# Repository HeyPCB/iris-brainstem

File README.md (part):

# Iris Brainstem

The power and servo hub in the base of Iris: 9 V USB-C PD in, a 6 V / 5 A servo rail laid in stitched copper zones, a 5 V rail, the half-duplex servo bus with ten ports, a speaker amp and a USB-C data port.

Part of [Iris, the human-eyed robot head](https://github.com/HeyPCB/iris), HeyPCB's open robot boards. Designed end to end with the HeyPCB method on
KiCad 10 (headless pipeline, Freerouting 2.4.1); every number below is measured on the files in this repository.
Mentions of `./run.sh`, `docs/rules/`, `blocks/` or `parts/` refer to the heypcb-kicad SDK that produced them.

| Layers | Outline | Parts | Nets | Connections routed | Vias | ERC errors | DRC errors / unconnected / parity |
|---|---|---|---|---|---|---|---|
| 4 | 64 x 80 mm, shaped | 97 | 48 | 230 -> 0 open | 208 | 0 | 0 / 0 / 0 |

**Not fabricated, assembled or powered.**

| | |
|---|---|
| KiCad project | [`kicad/`](kicad/) |
| Gerbers (unzipped and zipped), BOM, CPL, STEP, schematic PDF | [`fab/`](fab/) |
| Mechanism CAD, fit check and system docs | [Iris, the human-eyed robot head](https://github.com/HeyPCB/iris) |
| Renders | [top](media/top.png), [bottom](media/bottom.png) |
| Design process, every step as KiCad rendered it | [`media/design-process.mp4`](media/design-process.mp4) |

Iris Brainstem is board B2 of Iris, a robot head with human-like eyes. It sits flat in the base of
the head and is the head's power, USB and servo hub. It takes 9 V from a USB-C PD charger, makes a
6.0 V / 5 A rail for the ten eye, lid and brow servos and a 5 V rail for the head controller (B1
Cortex), measures the input with an INA226, drives the servos' half-duplex serial bus and the
speaker, and passes a second USB-C port's data up to B1. It was designed with the HeyPCB method on
KiCad 10 (10.0.6), by heypcb-kicad's headless pipeline with Freerouting 2.4.1, from the brief in
`board.json` and section 4.2 of the Iris design spec v0.1 (not published; its binding interconnect and mounting
contracts are in [the Iris system docs](https://github.com/HeyPCB/iris/blob/main/docs/system.md)).

**This board has not been fabricated, assembled or powered, and no firmware for it has been
written.** Everything below is what KiCad, the pipeline and the copper scripts measured on the
design files. Nothing here has been tested on hardware or in the head.

## Role in Iris

Iris has four boards (spec 4): **B1 Cortex** (ESP32-S3, camera, on the eye cradle), **B2
Brainstem** (this board, in the head's base), **B3 Iris ring** (two LED rings) and **B4 Brow**
(forehead sensors). B2 is where power enters the head and where every servo plugs in:

- USB-C **J1 PWR** brings 9 V. Everything in the head is powered from here.
- USB-C **J2 DATA** carries a PC's USB to B1's native USB, and its VBUS powers the logic on its own
  (servos stay off).
- **H1** (JST SH-10) and **H2** (JST SH-7) are the two harnesses to B1: 5V_SYS, USB, the servo bus
  and SERVO_EN on H1; I2C, the INA226's alert and I2S audio on H2 (spec 5).
- **J10-J19** are the servo ports, **J7** the speaker.

## Features

- **USB-C PD sink, 9 V, no firmware.** WCH CH224K (U1) with CFG1, CFG2 and CFG3 tied straight to
  GND, which requests 9 V. There is no configuration resistor to go missing: on the CH224K a
  missing resistor on CFG1 would request 20 V. VDD through 1 kOhm with 1 uF, VBUS sense through
  10 kOhm (WCH's reference schematic). A red **PD OK** LED (D6) hangs on the CH224K's PG output
  (open drain, active low).
- **Input protection and measurement.** SMAJ15A TVS (D1), 5 A Littelfuse NANO2 fuse (F1,
  0451005.MRL), 10 mOhm 1206 shunt (R1) read by an **INA226 at 0x40** (U2, ALERT on H2 pin 4), and
  470 uF on VIN (C3).
- **6V0_SERVO, 5 A.** TPS565208 buck (U3) to 5.93 V (68 k / 10 k on a 0.760 V reference), 3.3 uH
  FXL0630, 3 x 22 uF at the regulator and 470 uF at each servo bank (C1, C2). **Off by default**:
  EN is SERVO_EN from B1 through 1 kOhm with a 100 kOhm pull-down.
- **5V2 and 5V_SYS.** TPS56339 buck (U4) to 5.21 V (54.9 k / 10 k on 0.802 V), 5.6 uH FXL0630, then
  an SS34 (D2) onto 5V_SYS. J2's VBUS joins 5V_SYS through a second SS34 (D3). Neither VBUS is
  ever driven by the board. 5V_SYS goes to B1 on H1 pins 1-2 and to the amplifier.
- **3V3_B2.** AP2112K-3.3 (U6) from 5V_SYS for the INA226, the bus buffers and their pull-ups.
- **Servo bus.** The Waveshare / Feetech auto-direction half-duplex driver: 74LVC1G126 (U7),
  74LVC1G125 (U8) and an MMBT3906 (Q1), 10 k pull-ups on BUS_TX, BUS_RX and BUS_DATA, an ESD5Z5.0 on
  BUS_DATA at each bank (D4, D5). TX is never echoed back to RX.
- **Ten servo ports** (J10-J19), HC-5264-3A vertical (Molex 5264 type), pin 1 BUS_DATA, pin 2
  6V0_SERVO, pin 3 GND, in two banks of five down the left and right edges. **D V G** is printed at
  every port and each port is labelled with its servo ID.
- **Speaker amplifier.** MAX98357A (U9) on B1's I2S, mono (L+R)/2 (1 MOhm on SD_MODE), 9 dB gain,
  from 5V_SYS through a ferrite, to a JST SH-2 (J7). Bridge-tied output: neither wire is ground.
- **USB data port.** J2 with 5.1 kOhm on CC1 and CC2 (a plain sink) and a USBLC6-2SC6 (U5) on D+ /
  D- before H1.
- **Test pads** (1.5 mm, not fitted parts): VIN, 6V0, 5V2, 5V_SYS, 3V3_B2, BUS_DATA, SERVO_EN and
  GND (TP1-TP8).
- **Board:** 64.0 x 80.0 mm, corner fillet 3.0 mm, 1.6 mm, 4 copper layers: F.Cu signal and power
  zones, In1 a solid GND plane, In2 signal with a 6V0_SERVO pour, B.Cu mostly a power layer
  (6V0_SERVO, VIN and 5V_SYS zones, with keep-outs that hold signal tracks off them; 101.5 mm of
  track runs on B.Cu elsewhere). Every part is on the top side. Four non-plated 2.2 mm holes for
  M2 screws.

## Block diagram

```mermaid
flowchart LR
  J1["J1 USB-C PWR"] -->|"VBUS_PD 9 V"| D1["D1 SMAJ15A"]
  J1 -->|"CC, D+/D-"| U1["U1 CH224K<br/>CFG = 9 V"]
  U1 -->|PG| LED["D6 PD OK"]
  J1 -->|VBUS_PD| F1["F1 5 A"] --> R1["R1 10 mOhm"]
  R1 -->|VIN| C3["C3 470 uF"]
  R1 -.->|Kelvin| U2["U2 INA226 0x40"]
  R1 -->|VIN| U3["U3 TPS565208<br/>6V0 5 A"]
  R1 -->|VIN| U4["U4 TPS56339<br/>5V2 3 A"]
  U3 -->|6V0_SERVO| PORTS["J10-J19 servo ports<br/>C1, C2 470 uF"]
  U4 -->|5V2| D2["D2 SS34"] --> SYS(("5V_SYS"))
  J2["J2 USB-C DATA"] -->|VBUS_DATA| D3["D3 SS34"] --> SYS
  J2 -->|"D+/D-"| U5["U5 USBLC6"] --> H1["J5 H1 SH-10 to B1"]
  SYS --> H1
  SYS --> U6["U6 AP2112K 3V3_B2"]
  SYS --> U9["U9 MAX98357A"] --> J7["J7 SPK"]
  H1 -->|"BUS_TX / BUS_RX"| BUS["U7, U8, Q1<br/>half-duplex driver"] -->|BUS_DATA| PORTS
  H1 -->|SERVO_EN| U3
  H2["J6 H2 SH-7 to B1"] -->|I2C| U2
  U2 -->|"ALERT = nINT"| H2
  H2 -->|I2S| U9
```

## Power tree and what the copper carries

```
J1 VBUS_PD, 9 V ─┬─ D1 SMAJ15A to GND
                 └─ F1 5 A ─ R1 10 mOhm (INA226) ─ VIN ─┬─ C3 470 uF
                                                        ├─ U3 TPS565208 ─ 6V0_SERVO ─ C1, C2 470 uF ─ J10-J19 pin 2
                                                        └─ U4 TPS56339 ─ 5V2 ─ D2 SS34 ─┐
J2 VBUS_DATA, 5 V ─ D3 SS34 ────────────────────────────────────────────────────────────┴─ 5V_SYS

5V_SYS ─┬─ H1 pins 1-2 (to B1)
        ├─ FB1 ─ U9 MAX98357A ─ J7 speaker
        └─ U6 AP2112K ─ 3V3_B2
```

The input enters at the rear left (J1), and F1, R1 and C3 stand in one column above it. The servo
buck sits in the middle of the board, with its output node (L1, three 22 uF and C1) on the left,
and the ten ports run down both side edges. The 5V2 buck and the two diodes are at the rear right,
beside J2.

**Load figures** (spec 6, all estimates, none measured): VIN 0.68 A typical, about 4.3 A for
milliseconds (39 W); 6V0_SERVO 0.58 A typical, a 7-servo burst of 4.6 A for milliseconds, 9 A if
every servo stalls (beyond the buck's 5 A by design: firmware must cut torque); 5V_SYS 0.41 A
typical, 1.56 A peak. A 27 W (9 V, 3 A) PD charger is the spec's supply.

**Net classes** (from the brief; a class with a current is never narrowed by the routing ladder):
PDIN 0.6 mm (VBUS_PD, VIN_F, VIN; 0.6 mm is the receptacle's VBUS pads and the bucks' VIN pins),
SERVO 0.8 mm with 0.8 / 0.4 mm vias (6V0_SERVO), SWNODE 0.6 mm (the two switch nodes), RAIL5V
0.6 mm (5V2, 5V_SYS), USBVBUS 0.6 mm (VBUS_DATA). The tracks only connect the path. The current is
carried by the zones below.

### Power zones

After routing reaches 0 open, the pour stage lays the plan pours (GND on F.Cu, B.Cu and In1,
6V0_SERVO on In2) and then the brief's `board.zones`: each a named net's copper over a region on
chosen layers, above the plan pours, with every pad joined solid, and where the zone has a
`stitch` pitch, its own 0.6 / 0.3 mm via lattice. Board coordinates are mm from the outline's
top-left corner (y = 0 is the front edge). Every reason is also in `board.json`.

| Zone | Net | Layers | Region | Priority | Vias placed |
|---|---|---|---|---|---|
| `vbus_pd` | VBUS_PD | F.Cu, B.Cu | J1's VBUS pads, D1's cathode, F1's input pad (x 9.6-21.6, y 64.4-71.7) | 1 | 20 at 1.2 mm |
| `vin_f` | VIN_F | F.Cu | F1's output pad to R1, and the INA226's IN+ resistor (x 14.6-19.7, y 57.6-62.7) | 2 | - |
| `vin_col` | VIN | F.Cu, B.Cu | R1's VIN pad, C3's + pad, the INA226's IN- / VBUS taps (polygon in x 5.4-19.7, y 51.6-63.4) | 3 | 27 at 1.2 mm |
| `vin_band` | VIN | B.Cu | from the input column to both buck inputs (x 9.6-44.8, y 44.9-57.4) | 2 | - |
| `vin_u3`, `vin_u4` | VIN | F.Cu, B.Cu | each buck's VIN pin and input capacitors | 10 | 4 and 5 at 1.2 mm |
| `v6_b` | 6V0_SERVO | B.Cu | a U: the left bank strip, a bar along the front (y 7.3-12.5), the right bank strip | 5 | - |
| `v6_node` | 6V0_SERVO | F.Cu, B.Cu | L1's output pad, the three 22 uF and C1 (x 14.6-23.0, y 31.6-44.7) | 6 | 8 at 1.2 mm |
| `v6_bank_l`, `v6_bank_r`, `v6_c2` | 6V0_SERVO | F.Cu | the V pins of each bank (x 4.6-7.45 and 56.55-59.4, y 12.5-57.0) and C2 | 7, 8 | - |
| `gnd_out6`, `gnd_in6`, `gnd_in5` | GND | F.Cu | the GND sides of the servo buck's output and input capacitors and of the 5V2 buck's input | 9 | 12, 5 and 0 at 1.2 mm |
| `gnd_front`, `gnd_mid`, `gnd_rear` | GND | F.Cu, B.Cu | the front strip, the middle and the rear right, where the plan pour would otherwise have no vias | 0 | 16, 21 and 51 at 2.4 mm |
| `v5_spine` | 5V_SYS | B.Cu | from D2 / D3 at the rear, up the right of the middle (x 45.4-50.8) to H1 | 12 | - |
| `v5_front`, `v5_link_*` | 5V_SYS | F.Cu (+ B.Cu) | H1's pins 1-2, and the three places the spine meets F.Cu (D2, D3, H1) | 12, 13 | 3, 5 and 3 at 1.2 mm |
| `sw_6v0`, `sw_5v2` | SW_6V0, SW_5V2 | F.Cu | the gap between each buck's SW pin and its inductor | 11 | - |
| `v5v2_out` | 5V2 | F.Cu | L2's output pad, the two 22 uF and D2's anode (polygon in x 30.4-36.6, y 51.6-60.4), left of VIN's F.Cu track to U4 | 14 | - |

B.Cu is kept free of signal tracks under these zones by seven `board.keepouts` rectangles
(`bcu_*`), and In2 is kept free of tracks where the VBUS_PD, VIN and the servo buck's via fields
need room (`in2_*`): a stitch via must clear other nets' tracks on every layer. `gnd_in5` found no
via site (U4's GND pins reach In1 through the plan's own vias). Any GND zone stops the plan's GND
stitcher, so the plan's stitching count is 0 and the GND zones stitch themselves. The silkscreen
then displaced 25 GND stitching vias under its text, which leaves **208 vias** on the board (*read
off the board*: 206 of 0.6 / 0.3 mm and 2 of 0.8 / 0.4 mm; 53 of them are routing vias).

### Measured copper on the current path

`copper.py` (KiCad's Python) lists every track, via and pour of each power net on the final board
and exports the copper (tracks, pads, plan pours and zones) as polygons. `copper_cut.py` (any
Python with numpy and scipy) rasterises that copper on a 0.1 mm grid and finds, for each link of
the path, the **narrowest cross-section the link's whole current must pass**: a max-flow / min-cut
from the link's source pads to its sink pads, over every layer, with tracks, zones and via barrels
together, in parallel. Outer copper is taken as 35 um, inner as 17.5 um (JLCPCB's standard 4-layer
build), via plating as 25 um. Each cut is rated with `heypcb_kicad.route.ipc2221_amps` (IPC-2221,
I = k dT^0.44 A^0.725), per layer, summed. Each link is cut a second time with the copper within
1 mm of its pads counted as the pads ("beyond the pads"): that rates the board's own copper between
the parts, apart from the parts' fixed lands. Both scripts are copies of quack_core's, adapted.

| Link | From, to | Narrowest cross-section (35 um equivalent) | 10 C rise | **20 C rise** | Beyond the pads, 10 C / 20 C |
|---|---|---|---|---|---|
| VBUS_PD | J1 VBUS pads (A4, A9, B4, B9) to F1.1 | 1.15 mm of F.Cu, at the receptacle's VBUS pads | 2.6 A | **3.6 A** | 9.0 A / 12.2 A (6.23 mm) |
| VIN_F | F1.2 to R1.1 | 4.24 mm of F.Cu | 6.8 A | **9.2 A** | pads adjacent |
| VIN, both bucks | R1.2 to U3 and U4 VIN pins and their input capacitors | 5.09 mm of F.Cu | 7.8 A | **10.6 A** | 9.3 A / 12.6 A (In2 0.25, barrels 6.06) |
| VIN, servo buck | R1.2 to U3.3, C7.1, C8.1 | 3.08 mm: In2 0.39, 4 via barrels 2.69 | 5.5 A | **7.5 A** | 5.5 A / 7.5 A |
| SW_6V0 | U3.2 to L1.1 | 0.80 mm of F.Cu: U3's SW pin | 2.0 A | **2.8 A** | pads adjacent |
| 6V0_SERVO, all ports | L1.2 to J10-J19 pin 2 | 6.09 mm: F.Cu 0.70, 8 via barrels 5.39 | 10.0 A | **13.5 A** | 10.0 A / 13.5 A |
| 6V0_SERVO, each bank | L1.2 (with C11-C13, C1) to J10-J14 or J15-J19 pin 2 | 6.09 mm, the same section | 10.0 A | **13.5 A** | 10.0 A / 13.5 A |
| 6V0_SERVO, bank to bank | J10-J14 pin 2 to J15-J19 pin 2 | 7.61 mm: In2 2.82, B.Cu 4.78 | 10.0 A | **13.5 A** | 13.4 A / 18.2 A |
| GND, ports to servo buck | J10-J19 pin 3 to U3.1, C11-C13 pin 2 | 8.63 mm of F.Cu | 11.4 A | **15.5 A** | 13.3 A / 18.0 A |
| GND, servo buck to input | U3.1, C7.2, C8.2 to J1 GND pads | 2.97 mm of F.Cu | 5.3 A | **7.1 A** | 13.4 A / 18.2 A (F.Cu 5.74, barrels 2.69) |
| 5V2 | L2.2 to D2.2 (anode) | 1.04 mm of F.Cu | 2.5 A | **3.3 A** | 2.5 A / 3.3 A |
| 5V_SYS | D2.1, D3.1 (cathodes) to J5 pins 1-2 | 0.99 mm of F.Cu | 2.4 A | **3.2 A** | 2.4 A / 3.2 A |

*Read off the board* (`copper_cut.json`, `copper.json`) after the full run with
media. "Pads adjacent" means the two terminals are within 2 mm of each other, so the link is the
pads' own gap.

**What this says against spec 6.** At a 10 C rise on 1 oz outer copper:

- **The servo rail has about twice the copper its burst needs.** 6V0_SERVO from L1 to the ports
  rates 10.0 A (13.5 A at 20 C) against the 4.6 A burst and the buck's 5 A limit. The narrowest
  section is at L1's output node, where the F.Cu node meets the eight vias of `v6_node`; past that
  the current spreads over the B.Cu U, the In2 pour and the F.Cu bank strips. The GND return from
  the ports to the buck's output capacitors rates 11.4 A.
- **The input path carries the 4.3 A peak** at a 10 C rise on every board-copper link: VIN_F
  6.8 A, VIN to both bucks 7.8 A, VIN to the servo buck 5.5 A, the GND return from the buck input
  to J1 5.3 A (13.4 A beyond the pads).
- **Two links end on a part's own pins and rate lower by this rule.** VBUS_PD leaves the
  receptacle through its VBUS pads: 1.15 mm of copper at the pads' edges, 2.6 A at 10 C and 3.6 A
  at 20 C, against the 3 A PD contract and the millisecond 4.3 A peaks. Beyond the pads the zone
  is 6.23 mm (9.0 A). SW_6V0 is the TPS565208's 0.8 mm SW pin, 2.0 A by the chart against a 5 A
  switch current. Both are lands fixed by the footprint and well under 2 mm long; IPC-2221's chart
  is for long conductors, so these figures say little about the real limit, and neither was
  measured. The receptacle's current rating was not checked (see *Check before ordering*).
- **5V2 and 5V_SYS** rate 2.5 A and 2.4 A (3.3 A and 3.2 A at 20 C) against the 1.56 A peak.
  H1's two 5V_SYS pins are JST SH contacts rated 1 A each (catalogue rows), 2 A together, which
  the spec's 1.6 A respects.
- Via barrels are rated with the same formula as a plated wall; that is an approximation.

Nothing here is a measured temperature. Measure F1, R1, J1, U3, L1 and the port headers under the
real servo load before trusting any of it. The routed widths of the rest of the power nets, *read
off the board*: VBUS_DATA 0.6 mm (0.45 mm necks at pads, 2 vias), SW_5V2 0.6 mm plus its zone,
VIN's routed tracks 0.6 mm.

## Connectors and pinouts

Every connector follows spec 5 (binding). "Pin n" is pad n of the KiCad footprint. Both harness
cables are **double-ended, same direction** (pin n to pin n), 28 AWG, 150 mm. The SH headers are
side-entry with their mouths at the front edge; the board's header pin counts (10, 7, 2) all
differ, so no cable fits a wrong header.

### H1: J5, JST SH-10 (SM10B-SRSS-TB, C160409) to B1 J5

| Pin | Net | Direction | Level / type | Notes |
|---|---|---|---|---|
| 1 | 5V_SYS | B2 -> B1 | 4.85 V nominal (5V2 - SS34), <= 1.6 A total on pins 1-2 | source B2 |
| 2 | 5V_SYS | B2 -> B1 | as pin 1 | |
| 3 | GND | - | | |
| 4 | GND | - | | |
| 5 | USB_DN | both | USB 2.0 FS D-, 90 Ohm pair with 6 | ESD on B2 (U5); B1 GPIO19 |
| 6 | USB_DP | both | USB 2.0 FS D+ | B1 GPIO20 |
| 7 | GND | - | | separates the USB pair from the UART |
| 8 | BUS_TX | B1 -> B2 | 3.3 V UART, 1 Mbps, 8N1, idle high | B1 GPIO42 -> U7 A + Q1 base network (10 k pull-up on B2) |
| 9 | BUS_RX | B2 -> B1 | 3.3 V UART | U8 Y -> B1 GPIO44; 10 k pull-up on B2 |
| 10 | SERVO_EN | B1 -> B2 | 3.3 V CMOS, active high | -> U3 EN via 1 k; 100 k pull-down on B2 |

The board's nets carry the spec's names (USB_DN, USB_DP, BUS_TX and so on). The USB pair is routed
as two plain signals, without an impedance class (USB full speed). The mounting tabs are grounded.

### H2: J6, JST SH-7 (SM07B-SRSS-TB, C160406) to B1 J6

| Pin | Net | Direction | Level / type | Notes |
|---|---|---|---|---|
| 1 | GND | - | | |
| 2 | I2C_SDA | both | 3.3 V open drain, 400 kHz | pull-ups 2.2 k on B1 only (none on B2) |
| 3 | I2C_SCL | B1 -> | 3.3 V open drain | |
| 4 | nINT | B2 -> B1 | open drain, active low | INA226 ALERT; 10 k pull-up on B1 (GPIO3) |
| 5 | I2S_BCLK | B1 -> B2 | 3.3 V, 3.072 MHz (48 kHz x 64) | 33 Ohm series at B1; -> U9 BCLK |
| 6 | I2S_WS | B1 -> B2 | 3.3 V, 48 kHz | 33 Ohm series at B1; -> U9 LRCLK |
| 7 | I2S_AMP_SD | B1 -> B2 | 3.3 V I2S data | -> U9 DIN |

The mounting tabs are grounded.

### SPK: J7, JST SH-2 (SM02B-SRSS-TB, C160402)

Pin 1 OUTP (SPK_P, marked "+" on the silkscreen), pin 2 OUTN (SPK_N). A bridge-tied load:
**neither wire is ground.** 4-8 Ohm, about 1 W speaker (spec 5). The mounting tabs are grounded.

### USB-C: J1 PWR and J2 DATA (HRO TYPE-C-31-M-12, C165948)

- **J1 PWR.** CC1 / CC2 to the CH224K; VBUS to D1 and F1; D+ / D- to the CH224K's DP / DM (BC1.2
  only, not to B1).
- **J2 DATA.** CC1 / CC2 each 5.1 kOhm to GND; D+ / D- through U5 to H1 pins 6 / 5; VBUS through D3
  to 5V_SYS. The board never drives this VBUS.
- **J2 only** (a PC): logic runs, servos stay off (VIN reads 0 V). **J1 only:** everything runs,
  with no USB data. **Both:** 5V_SYS takes the higher of 5V2 and J2's VBUS, each through its own
  SS34.

### Servo ports: J10-J19 (HC-5264-3A, C2845815; footprint Molex_SPOX_5267-03A vertical)

| Pad | Net | Silkscreen | Notes |
|---|---|---|---|
| 1 | BUS_DATA | D | 3.3 V half-duplex, 1 Mbps; 10 k pull-up to 3V3_B2; ESD5Z5.0 at each bank |
| 2 | 6V0_SERVO | V | source B2 (U3); at most 1 A per port (stall) |
| 3 | GND | G | |

Watch the numbering: Feetech numbers the servo's own plug "1 GND, 2 Vcc, 3 Signal"; Waveshare
numbers the mating header "1 DATA, 2 VCC, 3 GND". The board follows Waveshare (pad 1 = DATA), as
spec 5 binds, and prints D / V / G beside every port. Pad 1 (square) is the outboard pin in both
banks.

**Port to servo ID (binding for firmware, spec 5), printed beside each port:**

| Port | J10 | J11 | J12 | J13 | J14 | J15 | J16 | J17 | J18 | J19 |
|---|---|---|---|---|---|---|---|---|---|---|
| Servo | ID 2 pan L | ID 5 upper lid L | ID 7 lower lid L | ID 9 brow L | ID 3 tilt | ID 1 pan R | ID 4 upper lid R | ID 6 lower lid R | ID 8 brow R | spare |
| Silk | J10 ID2 PAN L | J11 ID5 ULID L | J12 ID7 LLID L | J13 ID9 BROW L | J14 ID3 TILT | J15 ID1 PAN R | J16 ID4 ULID R | J17 ID6 LLID R | J18 ID8 BROW R | J19 SPARE |

### Test pads

| Pad | Net | Silkscreen | Board position (x, y) |
|---|---|---|---|
| TP1 | VIN | VIN | 12.80, 58.30 |
| TP2 | 6V0_SERVO | 6V0 | 21.55, 33.00 |
| TP3 | 5V2 | 5V2 | 28.00, 50.30 |
| TP4 | 5V_SYS | 5V | 40.90, 68.55 |
| TP5 | 3V3_B2 | 3V3 | 48.35, 62.35 |
| TP6 | BUS_DATA | BUS | 26.00, 17.10 |
| TP7 | SERVO_EN | EN | 29.40, 18.85 |
| TP8 | GND | GND | 22.60, 16.60 |

## Outline, holes and connector positions (for the mechanism CAD)

Board coordinates are mm from the outline's top-left corner, F face up; y = 0 is the front edge
(toward the face). The head frame H follows spec 4.2 (binding): **F face at Z = -60.0, Y = 32 - x,
X = -30 - y**. *Read off the board* with KiCad 10.0.6's `pcbnew`.

- **Outline:** 64.0 x 80.0 mm, fillet 3.0 mm, 1.6 mm thick. H: X -30 (front edge) to -110 (rear
  edge), Y +32 (x = 0, the robot's left) to -32.
- **Holes:** four 2.2 mm non-plated holes for M2 at (4, 4), (60, 4), (4, 76), (60, 76) = H (X, Y)
  (-34, +28), (-34, -28), (-106, +28), (-106, -28), onto the base plate's bosses (tops at Z -61.6).
  No track or via comes within 2.75 mm of a hole's centre.

| Part | Board centre (x, y), rotation | H (X, Y) of the centre | Extent on the board | Faces |
|---|---|---|---|---|
| J1 USB-C PWR | (17.00, 76.30), 0 | (-106.30, +15.00) | body x 12.53-21.47, y 72.65-79.95 | rear: mouth at the rear edge (H X -110), facing -X |
| J2 USB-C DATA | (47.00, 76.30), 0 | (-106.30, -15.00) | body x 42.53-51.47, y 72.65-79.95 | rear, as J1 |
| J5 H1 SH-10 | (38.50, 3.40), 180 | (-33.40, -6.50) | courtyard x 31.56-45.44, y 0.08-6.72; pin 1 at (43.00, 5.40) | front: mouth toward the front edge, facing +X |
| J6 H2 SH-7 | (23.50, 3.40), 180 | (-33.40, +8.50) | courtyard x 18.06-28.94, y 0.08-6.72; pin 1 at (26.50, 5.40) | front, as J5 |
| J7 SPK SH-2 | (13.00, 3.40), 180 | (-33.40, +19.00) | courtyard x 10.06-15.94, y 0.08-6.72; pin 1 at (13.50, 5.40) | front, as J5 |
| J10-J14 (left bank) | pin 1 at x 3.50, y 16.50 / 26.00 / 35.50 / 45.00 / 54.50 | pin 1 at Y +28.50, X -46.50 / -56.00 / -65.50 / -75.00 / -84.50 | pins at x 3.5, 6.0, 8.5; courtyards x 0.50-11.50, 6.0 mm deep in y | up (+Z), vertical headers |
| J15-J19 (right bank) | pin 1 at x 60.50, y 15.20 / 24.70 / 34.20 / 43.70 / 53.20 | pin 1 at Y -28.50, X -45.20 / -54.70 / -64.20 / -73.70 / -83.20 | pins at x 60.5, 58.0, 55.5; courtyards x 52.50-63.50 | up (+Z) |
| C1, C2 (470 uF, 6.3 x 7.7 mm cans) | (16.00, 31.00), (48.00, 31.00) | (-61.00, +16.00), (-61.00, -16.00) | courtyards 7.2 x 9.5 mm | |
| C3 (470 uF can) | (7.00, 64.00) | (-94.00, +25.00) | courtyard x 3.41-10.59, y 59.25-68.75 | |
| L1, L2 (FXL0630, 7 x 6.6 mm) | (24.30, 41.00), (38.30, 53.50) | (-71.00, +7.70), (-83.50, -6.30) | courtyards about 9 x 7.2 mm | |

Every part is on the F side. The tallest are the 5264 headers, the 470 uF cans and the
inductors; the spec allows 12 mm on F (Z -48). The through-hole tails of J10-J19 and the USB-C
receptacles' shell legs come through to the B side, where the spec allows 2 mm; their length below
the board was not checked. The pipeline's STEP (`fab/iris_brainstem.step`)
uses generated bodies, not vendor models, so take heights from the parts' drawings.

## Where the board differs from the spec

| Spec | On the board | Why |
|---|---|---|
| U5 USBLC6-2SC6 C2687116 (UMW) | **C7519**, STMicroelectronics' own USBLC6-2SC6 | The pinned table prefers ST's part over the clone; same pinout, same KiCad symbol |
| "PD OK" LED from 3V3_B2 through a resistor into PG | LED (D6) and 2.2 kOhm from the **CH224K's own VDD** into PG | With only J2 plugged in, 3V3_B2 is up while the CH224K is unpowered; an LED from 3V3_B2 into PG would back-feed the unpowered chip. From VDD it draws about 0.6 mA of the 5.7 mA the 1 kOhm VDD resistor supplies at 9 V |
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
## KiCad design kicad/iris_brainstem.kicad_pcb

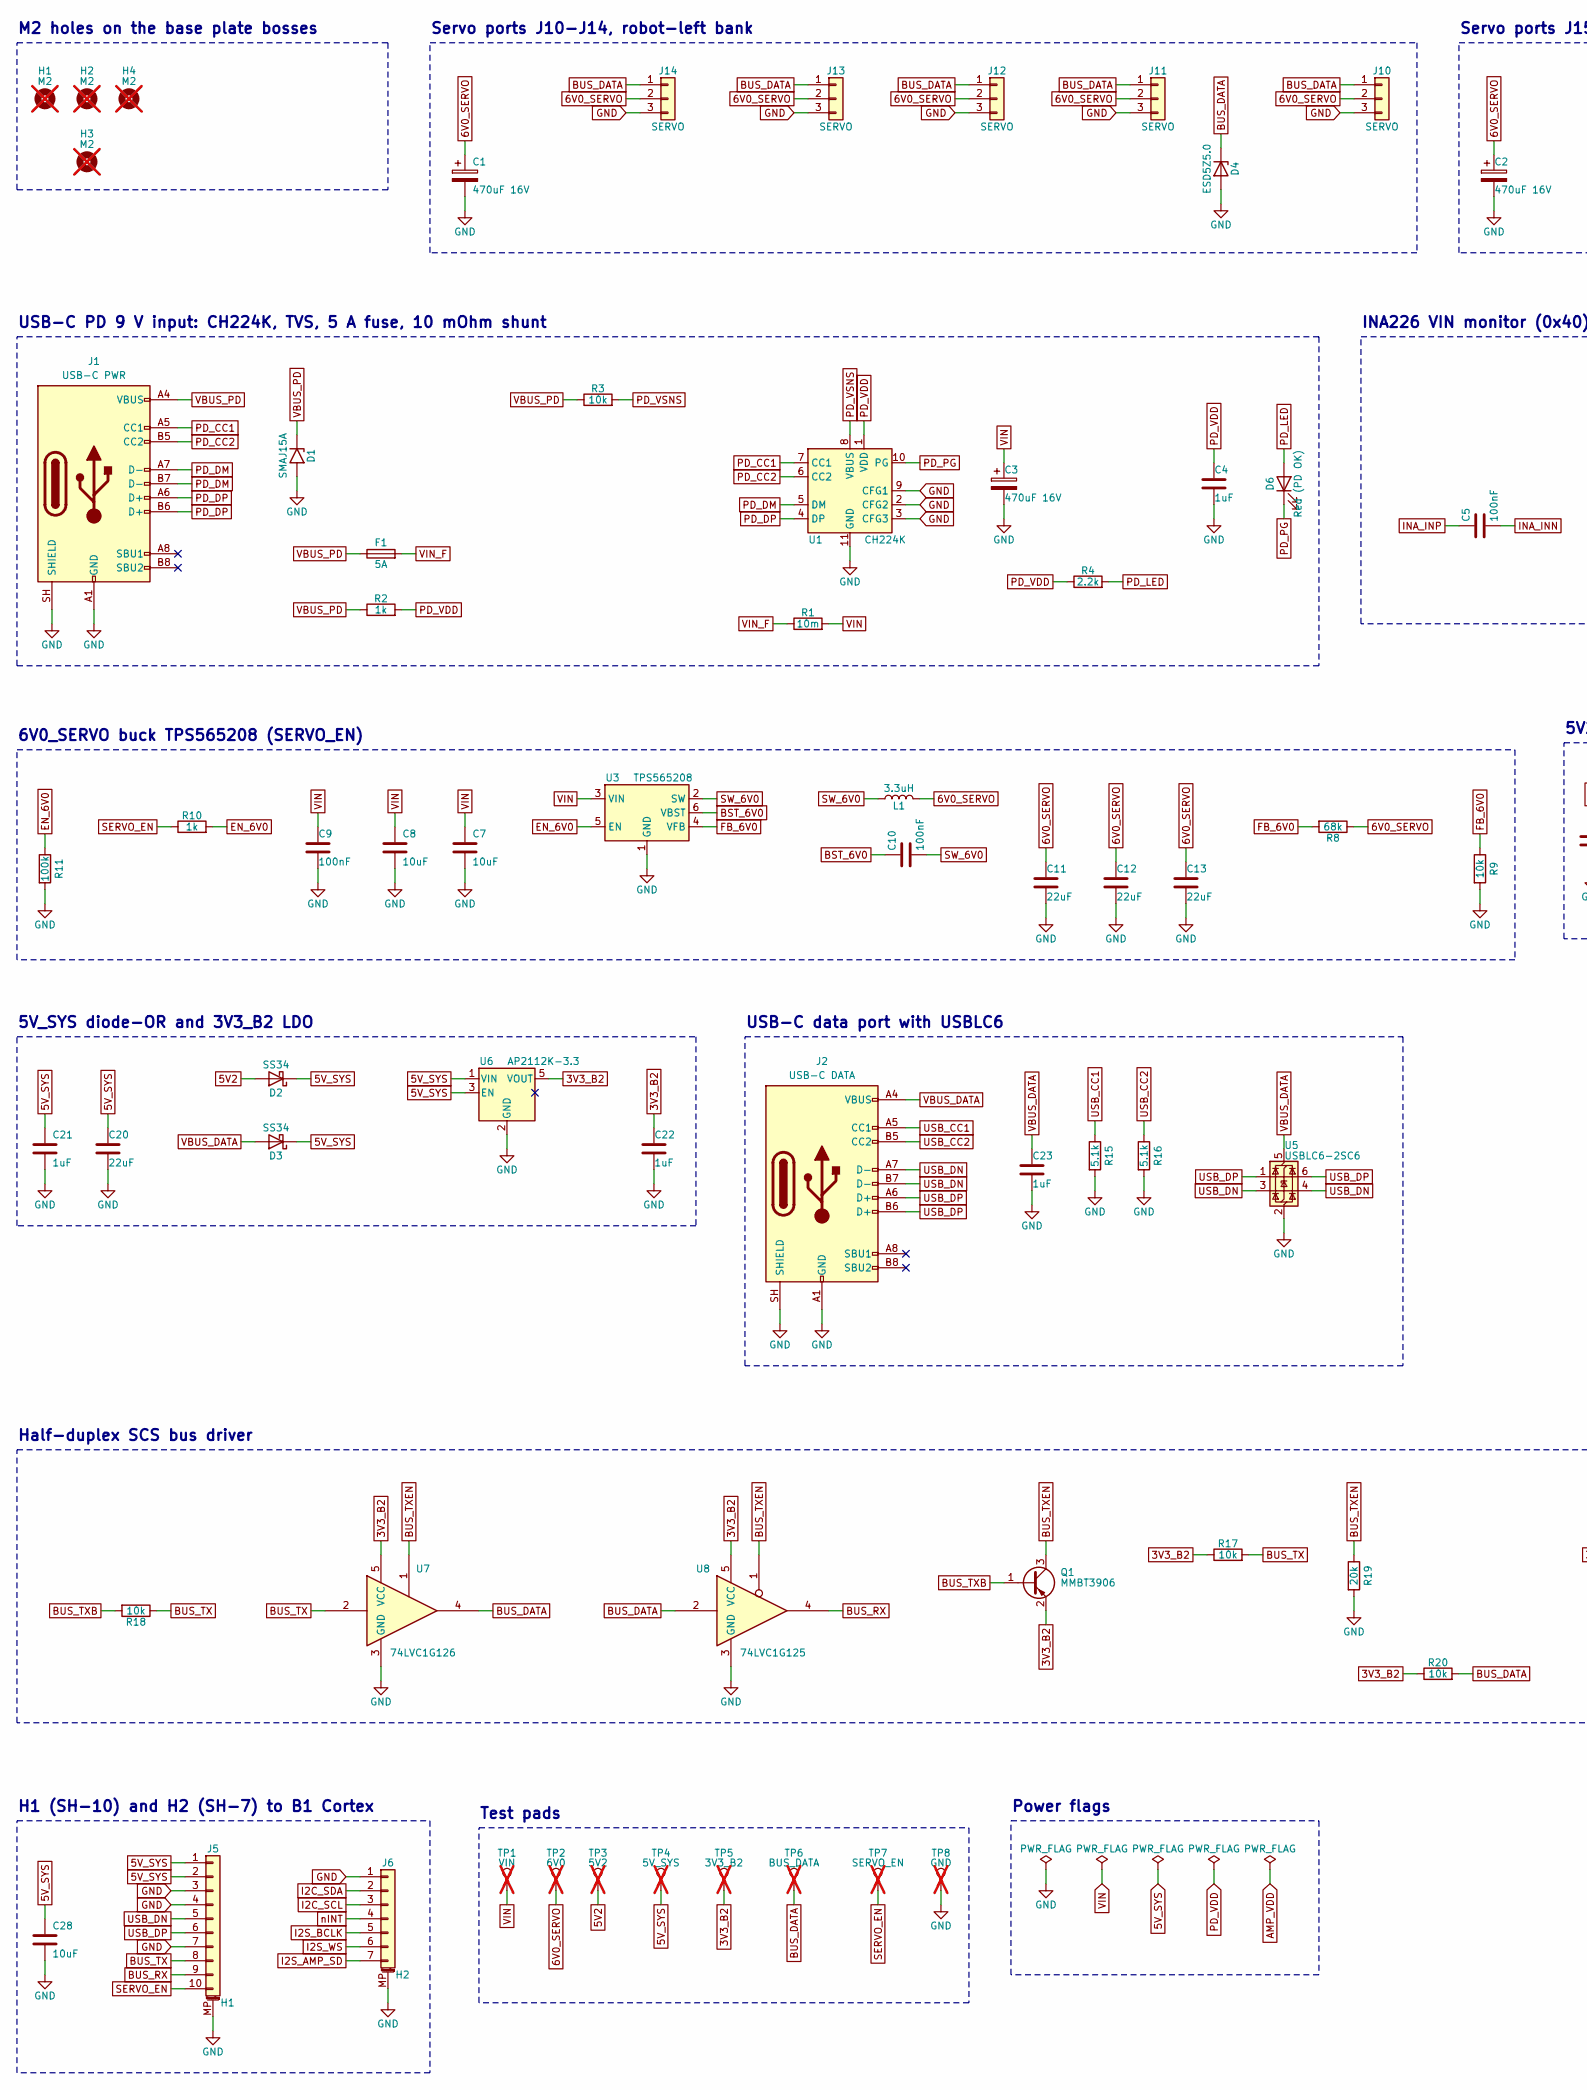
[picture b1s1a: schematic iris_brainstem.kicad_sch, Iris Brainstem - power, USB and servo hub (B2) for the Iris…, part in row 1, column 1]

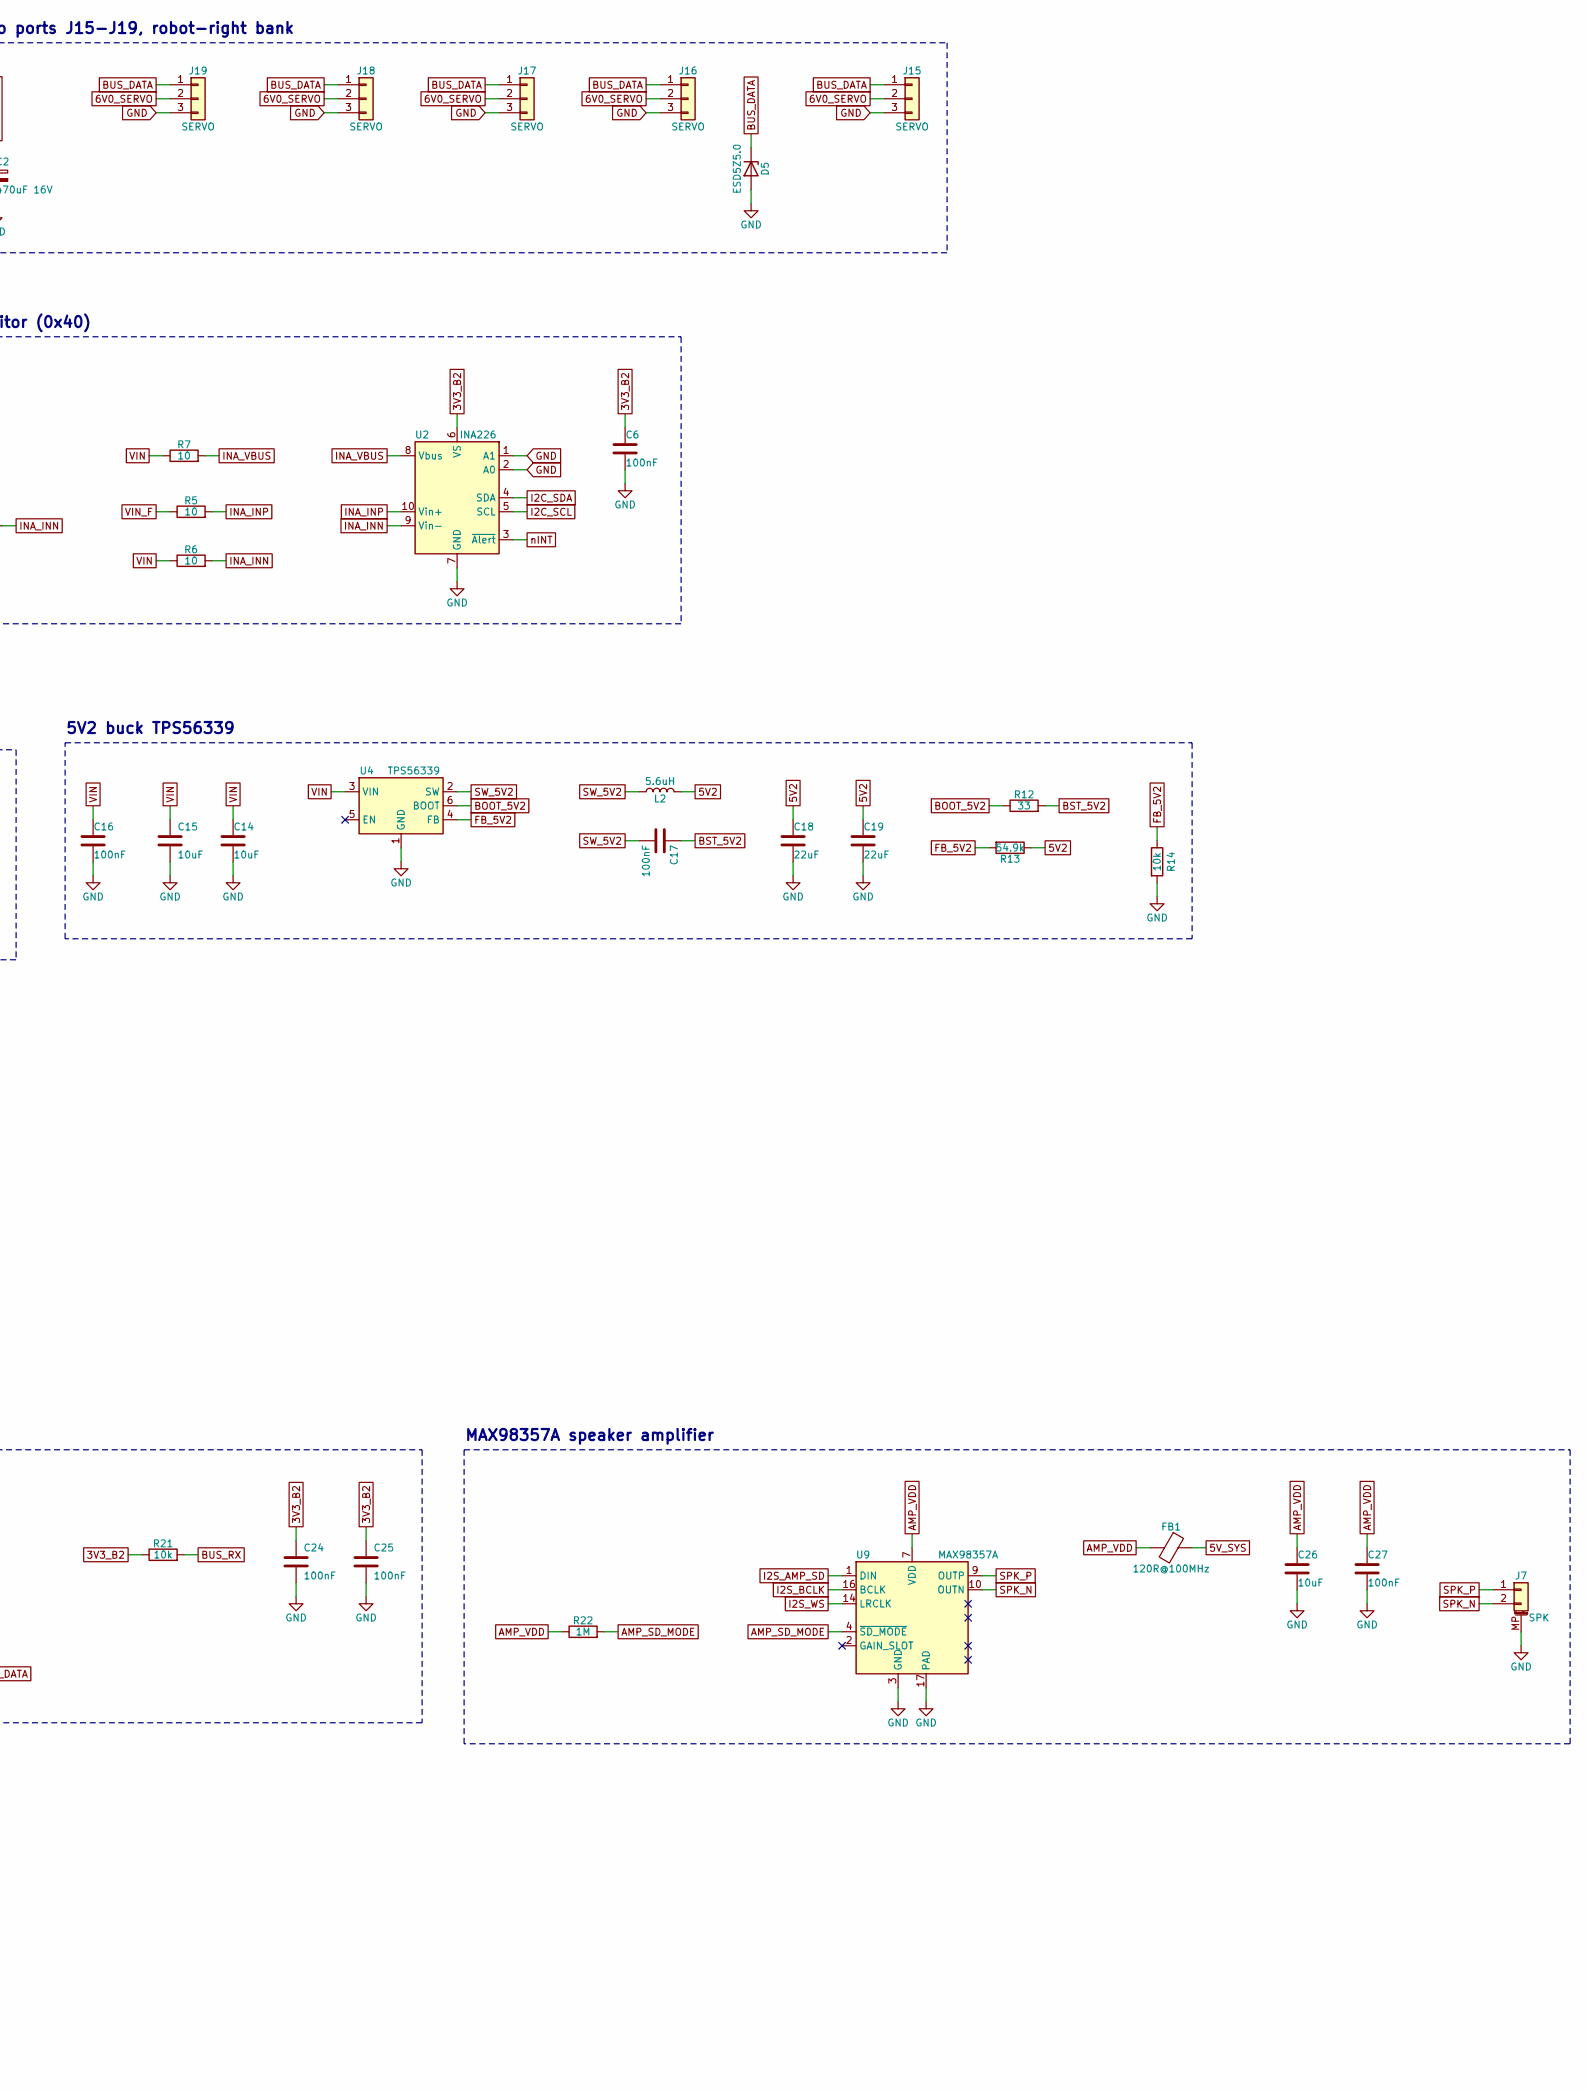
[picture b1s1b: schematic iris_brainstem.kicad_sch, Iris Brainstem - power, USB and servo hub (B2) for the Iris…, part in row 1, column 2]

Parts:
C1, C2, C3: 470uF 16V; CP_Elec_6.3x7.7; MPN RVT1C471M0607; LCSC C2977552
C4, C21, C22, C23: 1uF; C_0603_1608Metric; MPN CL10A105KB8NNNC; LCSC C15849
C5, C6, C9, C10, C16, C17, C24, C25, C27: 100nF; C_0603_1608Metric; MPN CC0603KRX7R9BB104; LCSC C14663
C7, C8, C14, C15, C26, C28: 10uF; C_0805_2012Metric; MPN CL21A106KAYNNNE; LCSC C15850
C11, C12, C13, C18, C19, C20: 22uF; C_0805_2012Metric; MPN CL21A226MAQNNNE; LCSC C45783
D1: SMAJ15A; D_SMA; MPN SMAJ15A; LCSC C19077535
D2, D3: SS34; D_SMA; MPN SS34; LCSC C8678
D4, D5: ESD5Z5.0; D_SOD-523; MPN ESD5Z5.0T1G; LCSC C82044
D6: Red (PD OK); LED_0603_1608Metric; MPN KT-0603R; LCSC C2286
F1: 5A; Fuse_Littelfuse-NANO2-451_453; MPN 0451005.MRL; LCSC C48467
FB1: 120R@100MHz; L_0603_1608Metric; MPN BLM18PG121SN1D; LCSC C14709
H1, H2, H3, H4: M2; MountingHole_2.2mm_M2; not fitted
J1: USB-C PWR; USB_C_Receptacle_HRO_TYPE-C-31-M-12; MPN TYPE-C-31-M-12; LCSC C165948
J2: USB-C DATA; USB_C_Receptacle_HRO_TYPE-C-31-M-12; MPN TYPE-C-31-M-12; LCSC C165948
J5: H1; JST_SH_SM10B-SRSS-TB_1x10-1MP_P1.00mm_Horizontal; MPN SM10B-SRSS-TB(LF)(SN); LCSC C160409
J6: H2; JST_SH_SM07B-SRSS-TB_1x07-1MP_P1.00mm_Horizontal; MPN SM07B-SRSS-TB(LF)(SN); LCSC C160406
J7: SPK; JST_SH_SM02B-SRSS-TB_1x02-1MP_P1.00mm_Horizontal; MPN SM02B-SRSS-TB(LF)(SN); LCSC C160402
J10, J11, J12, J13, J14, J15, J16, J17, J18, J19: SERVO; Molex_SPOX_5267-03A_1x03_P2.50mm_Vertical; MPN HC-5264-3A; LCSC C2845815
L1: 3.3uH; L_Changjiang_FXL0630; MPN FXL0630-3R3-M; LCSC C167219
L2: 5.6uH; L_Changjiang_FXL0630; MPN FXL0630-5R6-M; LCSC C475914
Q1: MMBT3906; SOT-23; MPN MMBT3906LT1G; LCSC C53444
R1: 10m; R_1206_3216Metric; MPN FMF06FTHR010-LH; LCSC C105362
R2, R10: 1k; R_0603_1608Metric; MPN 0603WAF1001T5E; LCSC C21190
R3, R9, R14, R17, R18, R20, R21: 10k; R_0603_1608Metric; MPN FRC0603F1002TS; LCSC C2906982
R4: 2.2k; R_0603_1608Metric; MPN 0603WAF2201T5E; LCSC C4190
R5, R6, R7: 10; R_1206_3216Metric; MPN 1206W4F100JT5E; LCSC C17903
R8: 68k; R_0603_1608Metric; MPN 0603WAF6802T5E; LCSC C23231
R11: 100k; R_0603_1608Metric; MPN 0603WAF1003T5E; LCSC C25803
R12: 33; R_0603_1608Metric; MPN 0603WAF330JT5E; LCSC C23140
R13: 54.9k; R_0603_1608Metric; MPN 0603WAF5492T5E; LCSC C23077
R15, R16: 5.1k; R_0603_1608Metric; MPN 0603WAF5101T5E; LCSC C23186
R19: 20k; R_0603_1608Metric; MPN 0603WAF2002T5E; LCSC C4184
R22: 1M; R_0603_1608Metric; MPN 0603WAF1004T5E; LCSC C22935
TP1: VIN; TestPoint_Pad_D1.5mm; not fitted
TP2: 6V0; TestPoint_Pad_D1.5mm; not fitted
TP3: 5V2; TestPoint_Pad_D1.5mm; not fitted
TP4: 5V_SYS; TestPoint_Pad_D1.5mm; not fitted
TP5: 3V3_B2; TestPoint_Pad_D1.5mm; not fitted
TP6: BUS_DATA; TestPoint_Pad_D1.5mm; not fitted
TP7: SERVO_EN; TestPoint_Pad_D1.5mm; not fitted
TP8: GND; TestPoint_Pad_D1.5mm; not fitted
U1: CH224K; SSOP-10-1EP_3.9x4.9mm_P1mm_EP2.1x3.3mm; MPN CH224K; LCSC C970725
U2: INA226; TSSOP-10_3x3mm_P0.5mm; MPN INA226AIDGSR; LCSC C49851
U3: TPS565208; SOT-23-6; MPN TPS565208DDCR; LCSC C2650336
U4: TPS56339; SOT-23-6; MPN TPS56339DDCR; LCSC C2071106
U5: USBLC6-2SC6; SOT-23-6; MPN USBLC6-2SC6; LCSC C7519
U6: AP2112K-3.3; SOT-23-5; MPN AP2112K-3.3TRG1; LCSC C51118
U7: 74LVC1G126; SOT-23-5; MPN SN74LVC1G126DBVR; LCSC C7834
U8: 74LVC1G125; SOT-23-5; MPN SN74LVC1G125DBVR; LCSC C23654
U9: MAX98357A; TQFN-16-1EP_3x3mm_P0.5mm_EP1.23x1.23mm; MPN MAX98357AETE+T; LCSC C910544

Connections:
3V3_B2: C6.1, C22.1, C24.1, C25.1, Q1.2 (E), R17.1, R20.1, R21.1, TP5.1, U2.6 (VS), U6.5 (VOUT), U7.5 (VCC), U8.5 (VCC)
5V2: C18.1, C19.1, D2.2 (A), L2.2, R13.1, TP3.1
5V_SYS: C20.1, C21.1, C28.1, D2.1 (K), D3.1 (K), FB1.1, J5.1, J5.2, TP4.1, U6.1 (VIN), U6.3 (EN)
6V0_SERVO: C1.1, C2.1, C11.1, C12.1, C13.1, J10.2, J11.2, J12.2, J13.2, J14.2, J15.2, J16.2, J17.2, J18.2, J19.2, L1.2, R8.1, TP2.1
AMP_SD_MODE: R22.2, U9.4 (~SD_MODE)
AMP_VDD: C26.1, C27.1, FB1.2, R22.1, U9.7 (VDD), U9.8 (VDD)
BOOT_5V2: R12.1, U4.6 (BOOT)
BST_5V2: C17.1, R12.2
BST_6V0: C10.1, U3.6 (VBST)
BUS_DATA: D4.1 (K), D5.1 (K), J10.1, J11.1, J12.1, J13.1, J14.1, J15.1, J16.1, J17.1, J18.1, J19.1, R20.2, TP6.1, U7.4, U8.2
BUS_RX: J5.9, R21.2, U8.4
BUS_TX: J5.8, R17.2, R18.1, U7.2
BUS_TXB: Q1.1 (B), R18.2
BUS_TXEN: Q1.3 (C), R19.1, U7.1, U8.1
EN_6V0: R10.2, R11.1, U3.5 (EN)
FB_5V2: R13.2, R14.1, U4.4 (FB)
FB_6V0: R8.2, R9.1, U3.4 (VFB)
GND: C1.2, C2.2, C3.2, C4.2, C6.2, C7.2, C8.2, C9.2, C11.2, C12.2, C13.2, C14.2, C15.2, C16.2, C18.2, C19.2, C20.2, C21.2, C22.2, C23.2, C24.2, C25.2, C26.2, C27.2, C28.2, D1.2 (A2), D4.2 (A), D5.2 (A), J1.A1 (GND), J1.A12 (GND), J1.B1 (GND), J1.B12 (GND), J1.SH (SHIELD), J2.A1 (GND), J2.A12 (GND), J2.B1 (GND), J2.B12 (GND), J2.SH (SHIELD), J5.3, J5.4, J5.7, J5.MP (MountPin), J6.1, J6.MP (MountPin), J7.MP (MountPin), J10.3, J11.3, J12.3, J13.3, J14.3, J15.3, J16.3, J17.3, J18.3, J19.3, R9.2, R11.2, R14.2, R15.2, R16.2, R19.2, TP8.1, U1.2 (CFG2), U1.3 (CFG3), U1.9 (CFG1), U1.11 (GND), U2.1 (A1), U2.2 (A0), U2.7 (GND), U3.1 (GND), U4.1 (GND), U5.2 (GND), U6.2 (GND), U7.3 (GND), U8.3 (GND), U9.3 (GND), U9.11 (GND), U9.15 (GND), U9.17 (PAD)
I2C_SCL: J6.3, U2.5 (SCL)
I2C_SDA: J6.2, U2.4 (SDA)
I2S_AMP_SD: J6.7, U9.1 (DIN)
I2S_BCLK: J6.5, U9.16 (BCLK)
I2S_WS: J6.6, U9.14 (LRCLK)
INA_INN: C5.2, R6.2, U2.9 (Vin-)
INA_INP: C5.1, R5.2, U2.10 (Vin+)
INA_VBUS: R7.2, U2.8 (Vbus)
PD_CC1: J1.A5 (CC1), U1.7 (CC1)
PD_CC2: J1.B5 (CC2), U1.6 (CC2)
PD_DM: J1.A7 (D-), J1.B7 (D-), U1.5 (DM)
PD_DP: J1.A6 (D+), J1.B6 (D+), U1.4 (DP)
PD_LED: D6.2 (A), R4.2
PD_PG: D6.1 (K), U1.10 (PG)
PD_VDD: C4.1, R2.2, R4.1, U1.1 (VDD)
PD_VSNS: R3.2, U1.8 (VBUS)
SERVO_EN: J5.10, R10.1, TP7.1
SPK_N: J7.2, U9.10 (OUTN)
SPK_P: J7.1, U9.9 (OUTP)
SW_5V2: C17.2, L2.1, U4.2 (SW)
SW_6V0: C10.2, L1.1, U3.2 (SW)
USB_CC1: J2.A5 (CC1), R15.1
USB_CC2: J2.B5 (CC2), R16.1
USB_DN: J2.A7 (D-), J2.B7 (D-), J5.5, U5.3 (I/O2), U5.4 (I/O2)
USB_DP: J2.A6 (D+), J2.B6 (D+), J5.6, U5.1 (I/O1), U5.6 (I/O1)
VBUS_DATA: C23.1, D3.2 (A), J2.A4 (VBUS), J2.A9 (VBUS), J2.B4 (VBUS), J2.B9 (VBUS), U5.5 (VBUS)
VBUS_PD: D1.1 (A1), F1.1, J1.A4 (VBUS), J1.A9 (VBUS), J1.B4 (VBUS), J1.B9 (VBUS), R2.1, R3.1
VIN: C3.1, C7.1, C8.1, C9.1, C14.1, C15.1, C16.1, R1.2, R6.1, R7.1, TP1.1, U3.3 (VIN), U4.3 (VIN)
VIN_F: F1.2, R1.1, R5.1
nINT: J6.4, U2.3 (~Alert)

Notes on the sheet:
M2 holes on the base plate bosses
Servo ports J10-J14, robot-left bank
Servo ports J15-J19, robot-right bank
USB-C PD 9 V input: CH224K, TVS, 5 A fuse, 10 mOhm shunt
INA226 VIN monitor (0x40)
6V0_SERVO buck TPS565208 (SERVO_EN)
5V2 buck TPS56339
5V_SYS diode-OR and 3V3_B2 LDO
USB-C data port with USBLC6
Half-duplex SCS bus driver
MAX98357A speaker amplifier
H1 (SH-10) and H2 (SH-7) to B1 Cortex
Test pads
Power flags

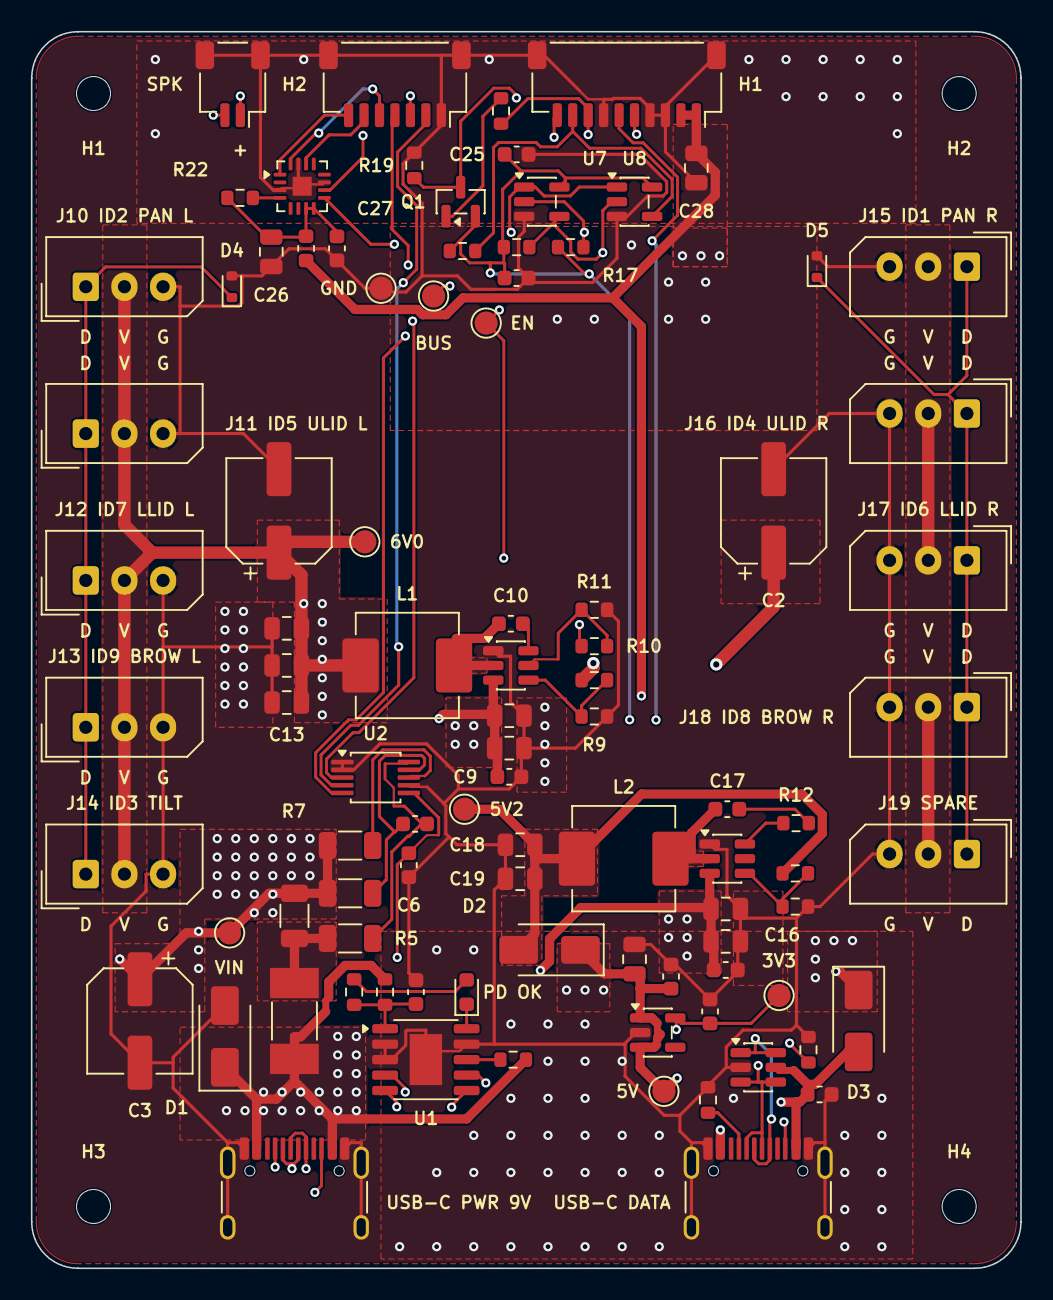
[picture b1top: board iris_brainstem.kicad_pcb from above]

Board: 4 copper layers, 64.0 x 80.0 mm, 97 parts (0 on the bottom side), 48 nets.

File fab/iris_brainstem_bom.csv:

"Reference","Value","Footprint","MPN","LCSC","Qty"
"C1,C2,C3","470uF 16V","Capacitor_SMD:CP_Elec_6.3x7.7","RVT1C471M0607","C2977552","3"
"C4,C21,C22,C23","1uF","Capacitor_SMD:C_0603_1608Metric","CL10A105KB8NNNC","C15849","4"
"C5,C6,C9,C10,C16,C17,C24,C25,C27","100nF","Capacitor_SMD:C_0603_1608Metric","CC0603KRX7R9BB104","C14663","9"
"C7,C8,C14,C15,C26,C28","10uF","Capacitor_SMD:C_0805_2012Metric","CL21A106KAYNNNE","C15850","6"
"C11,C12,C13,C18,C19,C20","22uF","Capacitor_SMD:C_0805_2012Metric","CL21A226MAQNNNE","C45783","6"
"D1","SMAJ15A","Diode_SMD:D_SMA","SMAJ15A","C19077535","1"
"D2,D3","SS34","Diode_SMD:D_SMA","SS34","C8678","2"
"D4,D5","ESD5Z5.0","Diode_SMD:D_SOD-523","ESD5Z5.0T1G","C82044","2"
"D6","Red (PD OK)","LED_SMD:LED_0603_1608Metric","KT-0603R","C2286","1"
"F1","5A","Fuse:Fuse_Littelfuse-NANO2-451_453","0451005.MRL","C48467","1"
"FB1","120R@100MHz","Inductor_SMD:L_0603_1608Metric","BLM18PG121SN1D","C14709","1"
"J1","USB-C PWR","Connector_USB:USB_C_Receptacle_HRO_TYPE-C-31-M-12","TYPE-C-31-M-12","C165948","1"
"J2","USB-C DATA","Connector_USB:USB_C_Receptacle_HRO_TYPE-C-31-M-12","TYPE-C-31-M-12","C165948","1"
"J5","H1","Connector_JST:JST_SH_SM10B-SRSS-TB_1x10-1MP_P1.00mm_Horizontal","SM10B-SRSS-TB(LF)(SN)","C160409","1"
"J6","H2","Connector_JST:JST_SH_SM07B-SRSS-TB_1x07-1MP_P1.00mm_Horizontal","SM07B-SRSS-TB(LF)(SN)","C160406","1"
"J7","SPK","Connector_JST:JST_SH_SM02B-SRSS-TB_1x02-1MP_P1.00mm_Horizontal","SM02B-SRSS-TB(LF)(SN)","C160402","1"
"J10,J11,J12,J13,J14,J15,J16,J17,J18,J19","SERVO","Connector_Molex:Molex_SPOX_5267-03A_1x03_P2.50mm_Vertical","HC-5264-3A","C2845815","10"
"L1","3.3uH","Inductor_SMD:L_Changjiang_FXL0630","FXL0630-3R3-M","C167219","1"
"L2","5.6uH","Inductor_SMD:L_Changjiang_FXL0630","FXL0630-5R6-M","C475914","1"
"Q1","MMBT3906","Package_TO_SOT_SMD:SOT-23","MMBT3906LT1G","C53444","1"
"R1","10m","Resistor_SMD:R_1206_3216Metric","FMF06FTHR010-LH","C105362","1"
"R2,R10","1k","Resistor_SMD:R_0603_1608Metric","0603WAF1001T5E","C21190","2"
"R3,R9,R14,R17,R18,R20,R21","10k","Resistor_SMD:R_0603_1608Metric","FRC0603F1002TS","C2906982","7"
"R4","2.2k","Resistor_SMD:R_0603_1608Metric","0603WAF2201T5E","C4190","1"
"R5,R6,R7","10","Resistor_SMD:R_1206_3216Metric","1206W4F100JT5E","C17903","3"
"R8","68k","Resistor_SMD:R_0603_1608Metric","0603WAF6802T5E","C23231","1"
"R11","100k","Resistor_SMD:R_0603_1608Metric","0603WAF1003T5E","C25803","1"
"R12","33","Resistor_SMD:R_0603_1608Metric","0603WAF330JT5E","C23140","1"
"R13","54.9k","Resistor_SMD:R_0603_1608Metric","0603WAF5492T5E","C23077","1"
"R15,R16","5.1k","Resistor_SMD:R_0603_1608Metric","0603WAF5101T5E","C23186","2"
"R19","20k","Resistor_SMD:R_0603_1608Metric","0603WAF2002T5E","C4184","1"
"R22","1M","Resistor_SMD:R_0603_1608Metric","0603WAF1004T5E","C22935","1"
"U1","CH224K","Package_SO:SSOP-10-1EP_3.9x4.9mm_P1mm_EP2.1x3.3mm","CH224K","C970725","1"
"U2","INA226","Package_SO:TSSOP-10_3x3mm_P0.5mm","INA226AIDGSR","C49851","1"
"U3","TPS565208","Package_TO_SOT_SMD:SOT-23-6","TPS565208DDCR","C2650336","1"
"U4","TPS56339","Package_TO_SOT_SMD:SOT-23-6","TPS56339DDCR","C2071106","1"
"U5","USBLC6-2SC6","Package_TO_SOT_SMD:SOT-23-6","USBLC6-2SC6","C7519","1"
"U6","AP2112K-3.3","Package_TO_SOT_SMD:SOT-23-5","AP2112K-3.3TRG1","C51118","1"
"U7","74LVC1G126","Package_TO_SOT_SMD:SOT-23-5","SN74LVC1G126DBVR","C7834","1"
"U8","74LVC1G125","Package_TO_SOT_SMD:SOT-23-5","SN74LVC1G125DBVR","C23654","1"
"U9","MAX98357A","Package_DFN_QFN:TQFN-16-1EP_3x3mm_P0.5mm_EP1.23x1.23mm","MAX98357AETE+T","C910544","1"

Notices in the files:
README.md:
Licence:
The Iris Brainstem design files in this folder (`board.json`, `copper.py`, `copper_cut.py`, this
README) and the `brainstem_*` blocks are released under the **CERN Open Hardware Licence Version 2 -
Strongly Reciprocal (CERN-OHL-S-2.0)**. KiCad's symbol, footprint and 3D libraries keep their own
licence (CC-BY-SA-4.0 with the KiCad library exception). Part numbers and stock figures are
catalogue facts.
kicad/iris_brainstem.kicad_pcb:
CERN-OHL-S-2.0
